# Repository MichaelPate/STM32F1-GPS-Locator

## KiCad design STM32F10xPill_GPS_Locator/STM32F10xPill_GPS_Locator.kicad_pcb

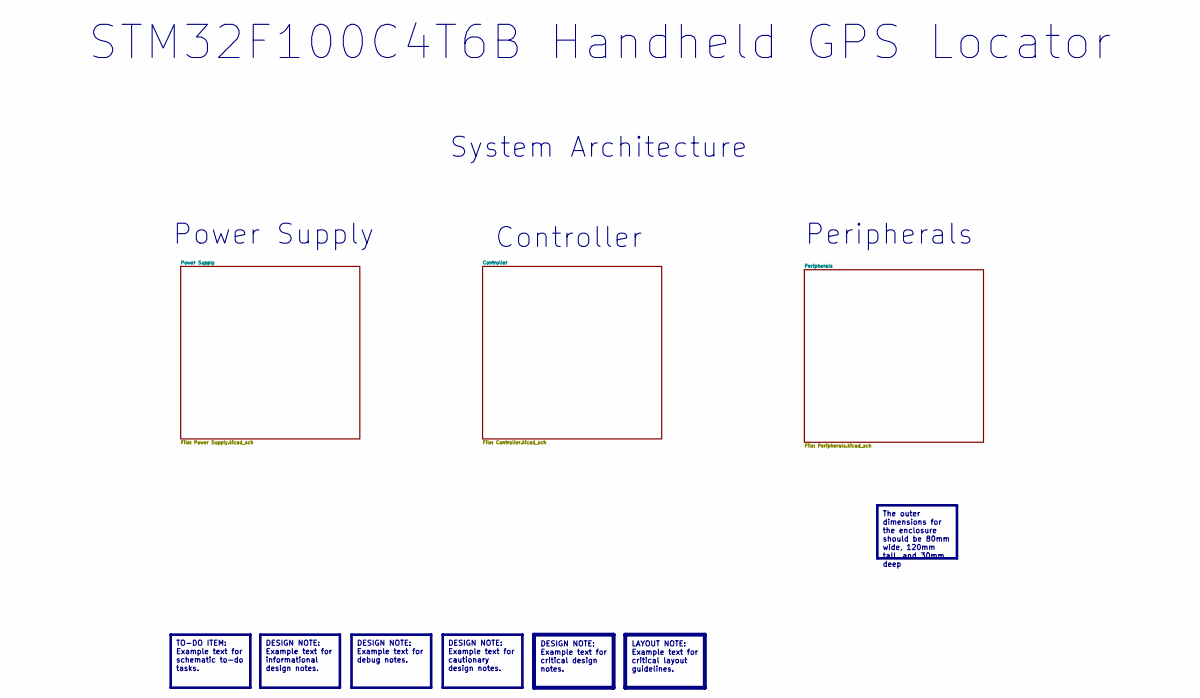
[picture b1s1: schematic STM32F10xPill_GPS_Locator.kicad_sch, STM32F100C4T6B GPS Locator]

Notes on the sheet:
STM32F100C4T6B Handheld GPS Locator
Peripherals
Controller
System Architecture
Power Supply
DESIGN NOTE: Example text for debug notes.
TO-DO ITEM: Example text for schematic to-do tasks.
The outer dimensions for the enclosure should be 80mm wide, 120mm tall, and 30mm deep
DESIGN NOTE: Example text for cautionary design notes.
DESIGN NOTE: Example text for critical design notes.
DESIGN NOTE: Example text for informational design notes.
LAYOUT NOTE: Example text for critical layout guidelines.

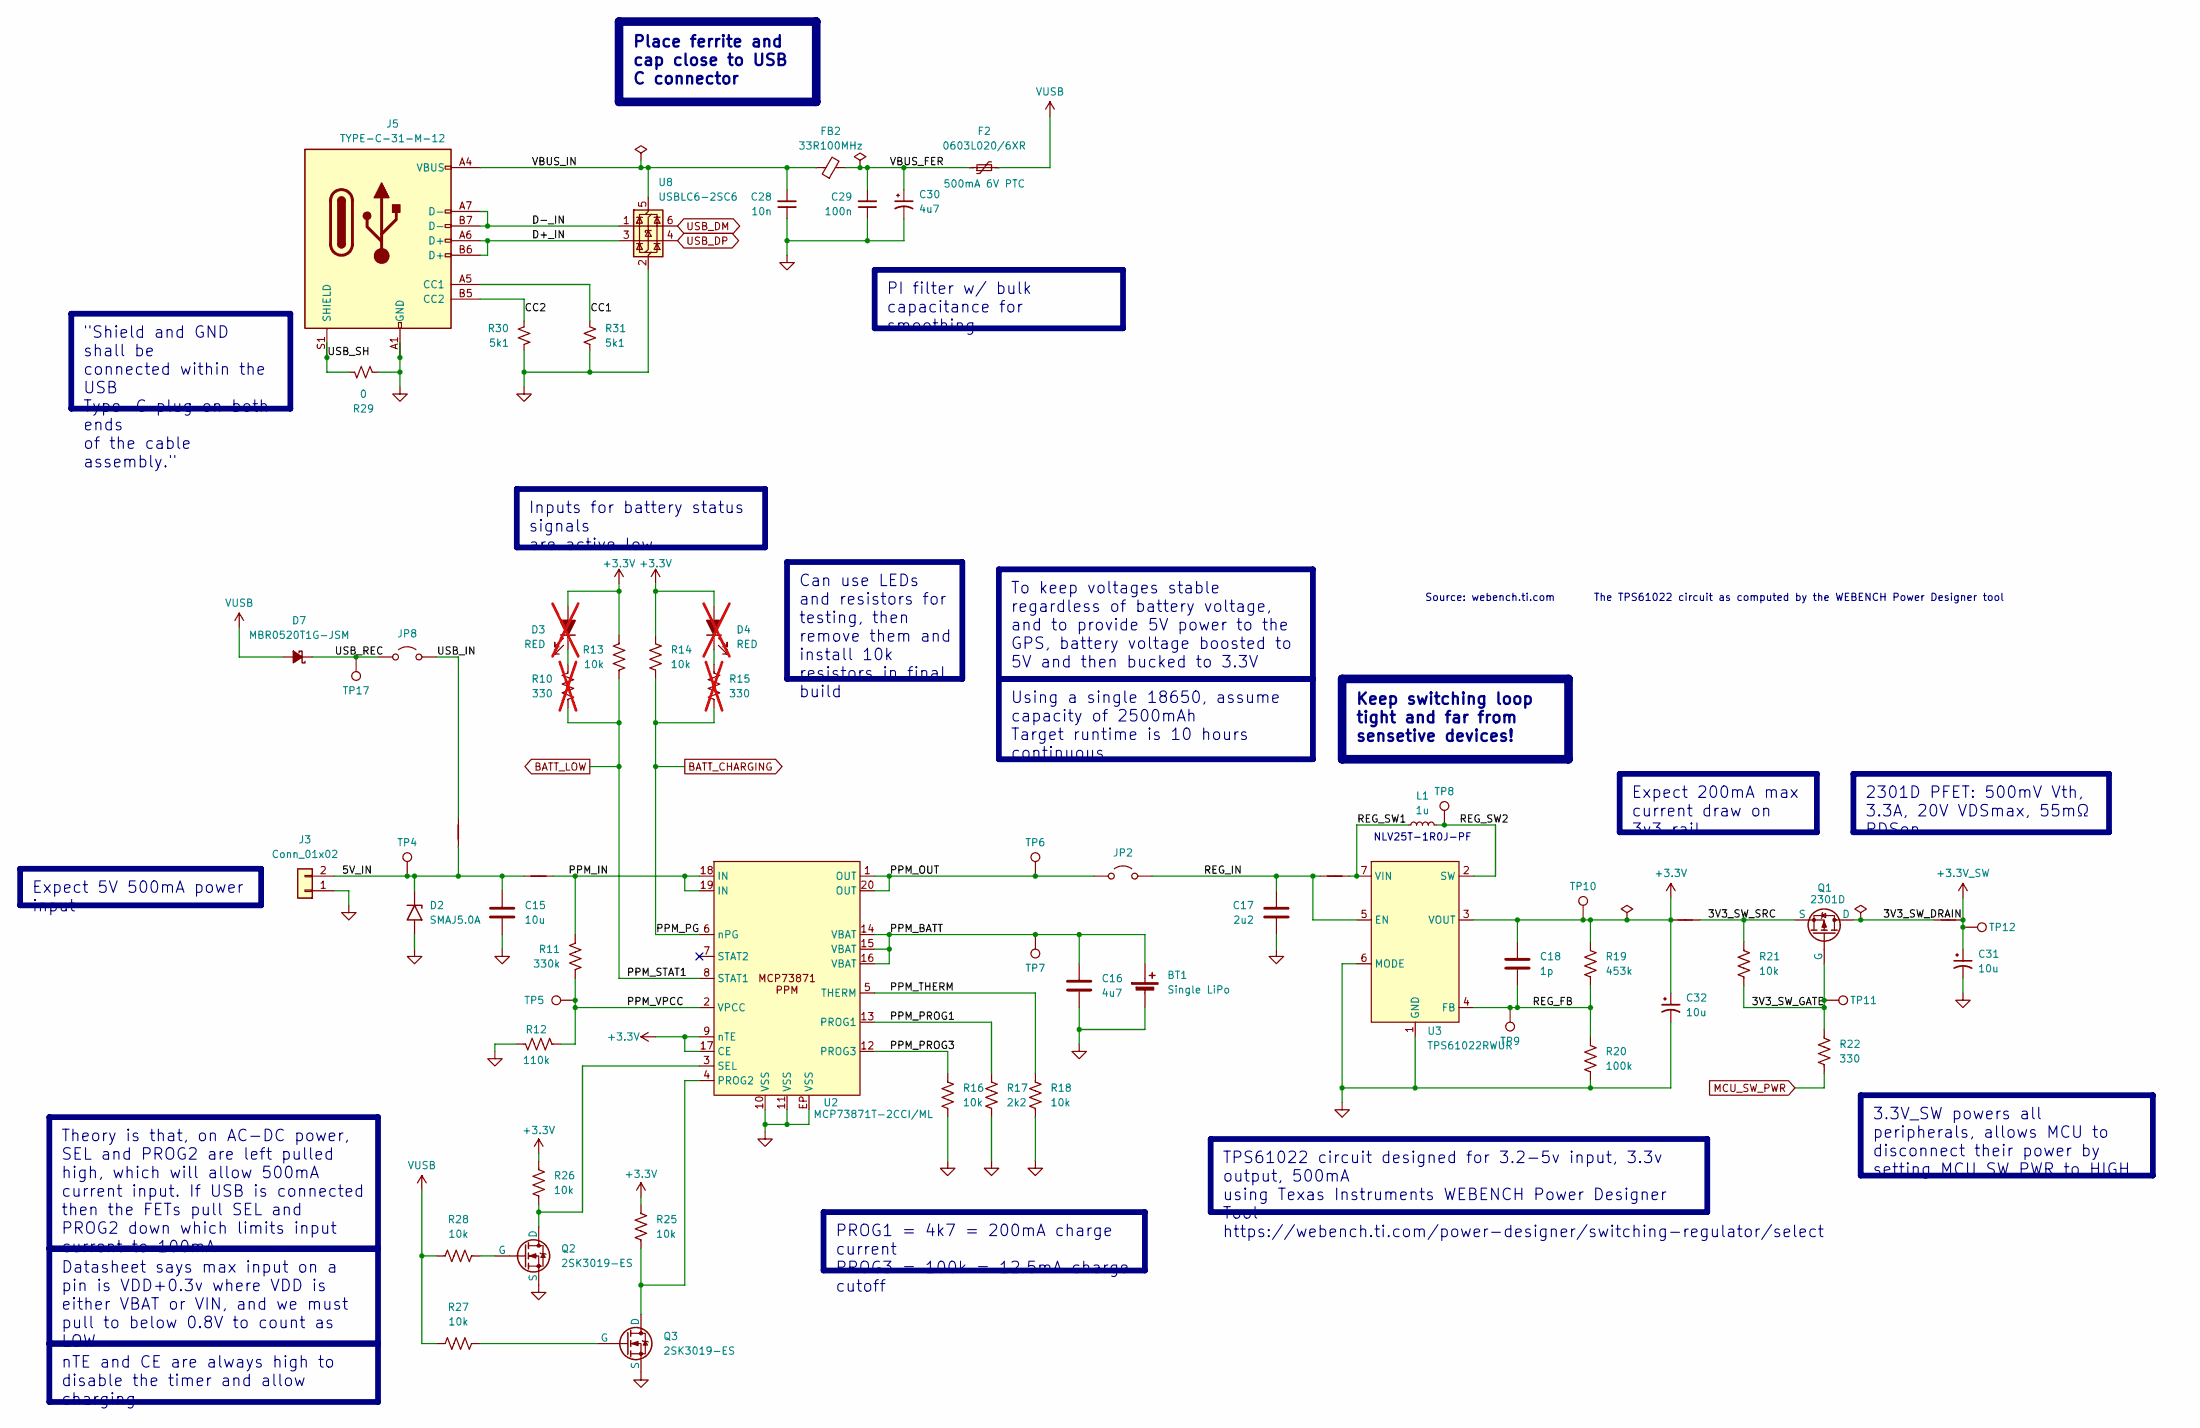
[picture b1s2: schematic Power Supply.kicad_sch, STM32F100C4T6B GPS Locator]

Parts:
BT1: Single LiPo; BatteryHolder_MPD_BH-18650-PC2
C15: 10u; C_0805_2012Metric
C16: 4u7; C_0805_2012Metric
C17: 2u2; C_0805_2012Metric
C18: 1p; C_0402_1005Metric
C28: 10n; C_0402_1005Metric
C29: 100n; C_0402_1005Metric
C30: 4u7; CP_Elec_4x5.4
C31, C32: 10u; CP_Elec_4x5.4
D2: SMAJ5.0A; D_SMA
D3, D4: RED; LED_0603_1608Metric; not fitted
D7: MBR0520T1G-JSM; D_SOD-123
F2: 0603L020/6XR; Fuse_0603_1608Metric_Pad1.05x0.95mm_HandSolder
FB2: 33R100MHz; L_0402_1005Metric
J3: Conn_01x02; JST_PH_B2B-PH-K_1x02_P2.00mm_Vertical
J5: TYPE-C-31-M-12; USB_C_Receptacle_HRO_TYPE-C-31-M-12; LCSC Part C165948
JP2, JP8: Jumper_2_Open; SolderJumper-2_P1.3mm_Open_Pad1.0x1.5mm
L1: 1u; L_1008_2520Metric; LCSC Part C76827
NT1, NT2, NT3, NT4, NT6: NetTie_2; NetTie-2_SMD_Pad0.5mm
Q1: 2301D; SOT-23; LCSC Part C7499855
Q2, Q3: 2SK3019-ES; SOT-523; LCSC Part 2SK3019-ES
R10, R15: 330; R_0402_1005Metric_Pad0.72x0.64mm_HandSolder; not fitted
R11: 330k; R_0402_1005Metric_Pad0.72x0.64mm_HandSolder
R12: 110k; R_0402_1005Metric_Pad0.72x0.64mm_HandSolder
R13, R14, R16, R18, R21, R25, R26, R27, R28: 10k; R_0402_1005Metric_Pad0.72x0.64mm_HandSolder
R17: 2k2; R_0402_1005Metric_Pad0.72x0.64mm_HandSolder
R19: 453k; R_0402_1005Metric_Pad0.72x0.64mm_HandSolder
R20: 100k; R_0402_1005Metric_Pad0.72x0.64mm_HandSolder
R22: 330; R_0402_1005Metric_Pad0.72x0.64mm_HandSolder
R29: 0; R_0402_1005Metric
R30, R31: 5k1; R_0402_1005Metric
TP4: 5V_IN; TestPoint_Pad_D1.5mm
TP5: PPM_VPCC; TestPoint_Pad_D1.5mm
TP6: PPM_OUT; TestPoint_Pad_D1.5mm
TP7: PPM_BATT; TestPoint_Pad_D1.5mm
TP8: REG_SW; TestPoint_Pad_D1.5mm
TP9: REG_FB; TestPoint_Pad_D1.5mm
TP10: REG_OUT; TestPoint_Pad_D1.5mm
TP11: 3V3_SW_GATE; TestPoint_Pad_D1.5mm
TP12: 3V3_SW; TestPoint_Pad_D1.5mm
TP17: USB_REC; TestPoint_Pad_D1.5mm
U2: MCP73871T-2CCI/ML; QFN-20-1EP_4x4mm_P0.5mm_EP2.5x2.5mm; LCSC Part C511310
U3: TPS61022RWUR; Texas_RWU0007A_VQFN-7_2x2mm_P0.5mm; LCSC Part C915088
U8: USBLC6-2SC6; SOT-23-6

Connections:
+3.3V: C18.2, C32.1, D3.2 (A), D4.2 (A), NT3.1, R13.2, R14.2, R19.2, R25.2, R26.2, TP10.1, U2.9 (nTE), U2.17 (CE), U3.3 (VOUT); also elsewhere on the board
+3.3V_SW: C31.1, NT4.2, TP12.1; also elsewhere on the board
/Power Supply/3V3_SW_DRAIN: NT4.1, Q1.1 (D)
/Power Supply/3V3_SW_GATE: Q1.2 (G), R21.1, R22.2, TP11.1
/Power Supply/3V3_SW_SRC: NT3.2, Q1.3 (S), R21.2
/Power Supply/5V_IN: C15.2, D2.1 (A1), J3.2, NT1.1, NT6.1, TP4.1
/Power Supply/CC1: J5.A5 (CC1), R31.2
/Power Supply/CC2: J5.B5 (CC2), R30.2
/Power Supply/D+_IN: J5.A6 (D+), J5.B6 (D+), U8.3 (I/O2)
/Power Supply/D-_IN: J5.A7 (D-), J5.B7 (D-), U8.1 (I/O1)
/Power Supply/PPM_BATT: BT1.1 (+), C16.2, TP7.1, U2.14 (VBAT), U2.15 (VBAT), U2.16 (VBAT)
/Power Supply/PPM_IN: NT1.2, R11.2, U2.18 (IN), U2.19 (IN)
/Power Supply/PPM_OUT: JP2.1 (A), TP6.1, U2.1 (OUT), U2.20 (OUT)
/Power Supply/PPM_PROG1: R17.2, U2.13 (PROG1)
/Power Supply/PPM_PROG3: R16.2, U2.12 (PROG3)
/Power Supply/PPM_THERM: R18.2, U2.5 (THERM)
/Power Supply/PPM_VPCC: R11.1, R12.1, TP5.1, U2.2 (VPCC)
/Power Supply/REG_FB: C18.1, R19.1, R20.2, TP9.1, U3.4 (FB)
/Power Supply/REG_IN: C17.2, JP2.2 (B), NT2.1, U3.5 (EN)
/Power Supply/REG_SW1: L1.2, NT2.2, U3.7 (VIN)
/Power Supply/REG_SW2: L1.1, TP8.1, U3.2 (SW)
/Power Supply/USB_IN: JP8.2 (B), NT6.2
/Power Supply/USB_REC: D7.1 (K), JP8.1 (A), TP17.1
/Power Supply/USB_SH: J5.S1 (SHIELD), R29.1
/Power Supply/VBUS_FER: C29.2, C30.1, F2.1, FB2.2
/Power Supply/VBUS_IN: C28.2, FB2.1, J5.A4 (VBUS), J5.A9 (VBUS), J5.B4 (VBUS), J5.B9 (VBUS), U8.5 (VBUS)
BATT_CHARGING: R14.1, R15.1, U2.6 (nPG); also elsewhere on the board
BATT_LOW: R10.1, R13.1, U2.8 (STAT1); also elsewhere on the board
GND: BT1.2 (-), C15.1, C16.1, C17.1, C28.1, C29.1, C30.2, C31.2, C32.2, D2.2 (A2), J3.1, J5.A1 (GND), J5.A12 (GND), J5.B1 (GND), J5.B12 (GND), Q2.3 (S), Q3.3 (S), R12.2, R16.1, R17.1, R18.1, R20.1, R29.2, R30.1, R31.1, U2.10 (VSS), U2.11 (VSS), U2.EP (VSS), U3.1 (GND), U3.6 (MODE), U8.2 (GND); also elsewhere on the board
MCU_SW_PWR: R22.1
unnamed: D3.1 (K), R10.2
unnamed: D4.1 (K), R15.2
unnamed: Q2.1 (D), R26.1, U2.3 (SEL)
unnamed: Q2.2 (G), R28.1
unnamed: Q3.1 (D), R25.1, U2.4 (PROG2)
unnamed: Q3.2 (G), R27.1
USB_DM: U8.6 (I/O1); also elsewhere on the board
USB_DP: U8.4 (I/O2); also elsewhere on the board
VUSB: D7.2 (A), F2.2, R27.2, R28.2

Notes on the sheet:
NLV25T-1R0J-PF
Source: webench.ti.com The TPS61022 circuit as computed by the WEBENCH Power Designer tool
2301D PFET: 500mV Vth, 3.3A, 20V VDSmax, 55mΩ RDSon
PROG1 = 4k7 = 200mA charge current PROG3 = 100k = 12.5mA charge cutoff
Inputs for battery status signals are active low
"Shield and GND shall be connected within the USB Type-C plug on both ends of the cable assembly."
Datasheet says max input on a pin is VDD+0.3v where VDD is either VBAT or VIN, and we must pull to below 0.8V to count as LOW
nTE and CE are always high to disable the timer and allow charging
Expect 200mA max current draw on 3v3 rail
Expect 5V 500mA power input
PI filter w/ bulk capacitance for smoothing
Using a single 18650, assume capacity of 2500mAh Target runtime is 10 hours continuous
To keep voltages stable regardless of battery voltage, and to provide 5V power to the GPS, battery voltage boosted to 5V and then bucked to 3.3V
Theory is that, on AC-DC power, SEL and PROG2 are left pulled high, which will allow 500mA current input. If USB is connected then the FETs pull SEL and PROG2 down which limits input current to 100mA
Can use LEDs and resistors for testing, then remove them and install 10k resistors in final build
3.3V_SW powers all peripherals, allows MCU to disconnect their power by setting MCU_SW_PWR to HIGH
Keep switching loop tight and far from sensetive devices!
Place ferrite and cap close to USB C connector
TPS61022 circuit designed for 3.2-5v input, 3.3v output, 500mA using Texas Instruments WEBENCH Power Designer Tool https://webench.ti.com/power-designer/switching-regulator/select

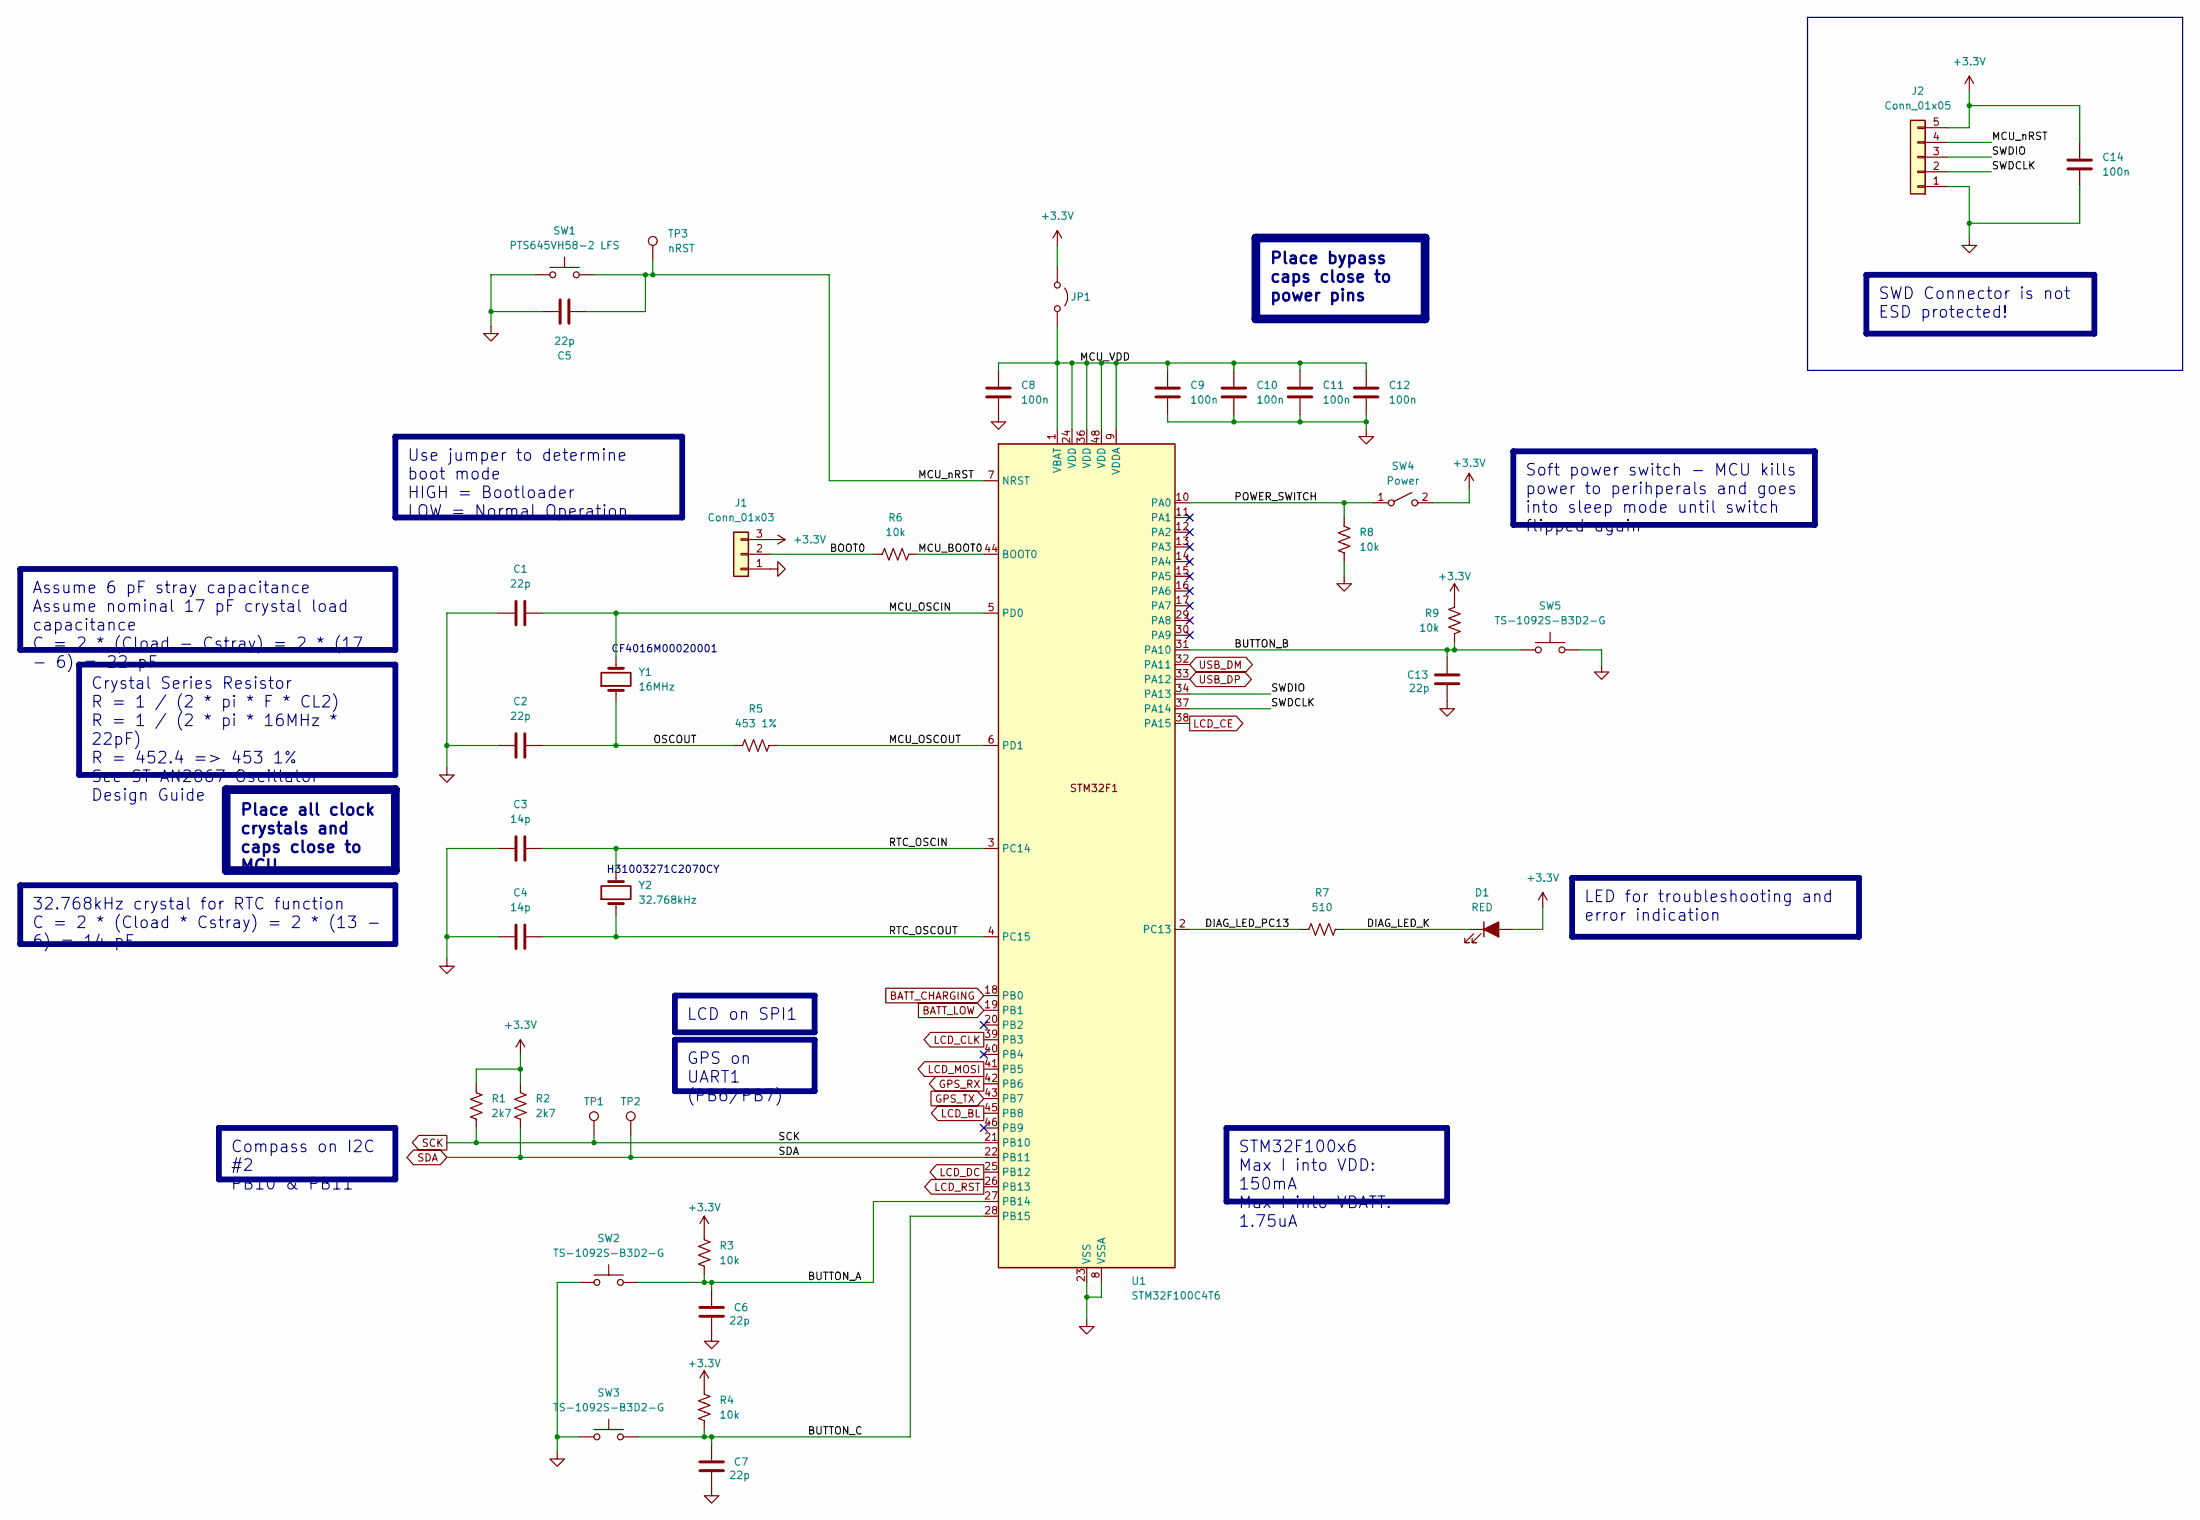
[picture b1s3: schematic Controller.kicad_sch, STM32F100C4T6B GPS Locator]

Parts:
C1, C2, C5, C6, C7, C13: 22p; C_0402_1005Metric
C3, C4: 14p; C_0402_1005Metric
C8: 100n; C_0603_1608Metric
C9, C10, C11, C12, C14: 100n; C_0402_1005Metric
D1: RED; LED_0603_1608Metric
J1: Conn_01x03; PinHeader_1x03_P2.54mm_Horizontal
J2: Conn_01x05; PinHeader_1x05_P2.54mm_Horizontal
JP1: Jumper_2_Open; SolderJumper-2_P1.3mm_Open_Pad1.0x1.5mm
R1, R2: 2k7; R_0402_1005Metric_Pad0.72x0.64mm_HandSolder
R3, R4, R6, R8, R9: 10k; R_0402_1005Metric_Pad0.72x0.64mm_HandSolder
R5: 453 1%; R_0402_1005Metric_Pad0.72x0.64mm_HandSolder
R7: 510; R_0402_1005Metric_Pad0.72x0.64mm_HandSolder
SW1: PTS645VH58-2 LFS; SW_Tactile_SPST_Angled_PTS645Vx58-2LFS; Digikey Part CKN9120-ND
SW2, SW3, SW5: TS-1092S-B3D2-G; SW_Tactile_SPST_NO_Straight_CK_PTS636Sx25SMTRLFS; LCSC Part C520860
SW4: Power; JST_PH_B2B-PH-K_1x02_P2.00mm_Vertical
TP1: SCK; TestPoint_Pad_D1.5mm
TP2: SDA; TestPoint_Pad_D1.5mm
TP3: nRST; TestPoint_Pad_D1.5mm
U1: STM32F100C4T6; LQFP-48_7x7mm_P0.5mm
Y1: 16MHz; Crystal_SMD_3225-4Pin_3.2x2.5mm; LCSC Part C7464895
Y2: 32.768kHz; Crystal_SMD_3215-2Pin_3.2x1.5mm; LCSC Part C5361379

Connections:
+3.3V: C14.2, D1.2 (A), J1.3, J2.5, JP1.1 (A), R1.2, R2.2, R3.2, R4.2, R9.2, SW4.2 (B); also elsewhere on the board
/Controller/BOOT0: J1.2, R6.1
/Controller/BUTTON_A: C6.2, R3.1, SW2.2, U1.27 (PB14)
/Controller/BUTTON_B: C13.2, R9.1, SW5.2, U1.31 (PA10)
/Controller/BUTTON_C: C7.2, R4.1, SW3.2, U1.28 (PB15)
/Controller/DIAG_LED_K: D1.1 (K), R7.1
/Controller/DIAG_LED_PC13: R7.2, U1.2 (PC13)
/Controller/MCU_BOOT0: R6.2, U1.44 (BOOT0)
/Controller/MCU_OSCIN: C1.2, U1.5 (PD0), Y1.3
/Controller/MCU_OSCOUT: R5.2, U1.6 (PD1)
/Controller/MCU_VDD: C8.2, C9.2, C10.2, C11.2, C12.2, JP1.2 (B), U1.1 (VBAT), U1.9 (VDDA), U1.24 (VDD), U1.36 (VDD), U1.48 (VDD)
/Controller/MCU_nRST: C5.2, J2.4, SW1.2, TP3.1, U1.7 (NRST)
/Controller/OSCOUT: C2.2, R5.1, Y1.1
/Controller/POWER_SWITCH: R8.2, SW4.1 (A), U1.10 (PA0)
/Controller/RTC_OSCIN: C3.2, U1.3 (PC14), Y2.2
/Controller/RTC_OSCOUT: C4.2, U1.4 (PC15), Y2.1
/Controller/SWDCLK: J2.2, U1.37 (PA14)
/Controller/SWDIO: J2.3, U1.34 (PA13)
BATT_CHARGING: U1.18 (PB0); also elsewhere on the board
BATT_LOW: U1.19 (PB1); also elsewhere on the board
GND: C1.1, C2.1, C3.1, C4.1, C5.1, C6.1, C7.1, C8.1, C9.1, C10.1, C11.1, C12.1, C13.1, C14.1, J1.1, J2.1, R8.1, SW1.1, SW2.1, SW3.1, SW5.1, U1.8 (VSSA), U1.23 (VSS), U1.35 (VSS), U1.47 (VSS); also elsewhere on the board
GPS_RX: U1.42 (PB6)
GPS_TX: U1.43 (PB7); also elsewhere on the board
LCD_BL: U1.45 (PB8); also elsewhere on the board
LCD_CE: U1.38 (PA15); also elsewhere on the board
LCD_CLK: U1.39 (PB3); also elsewhere on the board
LCD_DC: U1.25 (PB12); also elsewhere on the board
LCD_MOSI: U1.41 (PB5); also elsewhere on the board
LCD_RST: U1.26 (PB13); also elsewhere on the board
SCK: R1.1, TP1.1, U1.21 (PB10); also elsewhere on the board
SDA: R2.1, TP2.1, U1.22 (PB11); also elsewhere on the board
USB_DM: U1.32 (PA11); also elsewhere on the board
USB_DP: U1.33 (PA12); also elsewhere on the board

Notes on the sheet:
H31003271C2070CY
CF4016M00020001
Crystal Series Resistor R = 1 / (2 * pi * F * CL2) R = 1 / (2 * pi * 16MHz * 22pF) R = 452.4 => 453 1% See ST AN2867 Oscillator Design Guide
Place all clock crystals and caps close to MCU
STM32F100x6 Max I into VDD: 150mA Max I into VBATT: 1.75uA
Soft power switch - MCU kills power to perihperals and goes into sleep mode until switch flipped again
LCD on SPI1
Compass on I2C #2 PB10 & PB11
GPS on UART1 (PB6/PB7)
Place bypass caps close to power pins
Use jumper to determine boot mode HIGH = Bootloader LOW = Normal Operation
LED for troubleshooting and error indication
Assume 6 pF stray capacitance Assume nominal 17 pF crystal load capacitance C = 2 * (Cload - Cstray) = 2 * (17 - 6) = 22 pF
SWD Connector is not ESD protected!
32.768kHz crystal for RTC function C = 2 * (Cload * Cstray) = 2 * (13 - 6) = 14 pF

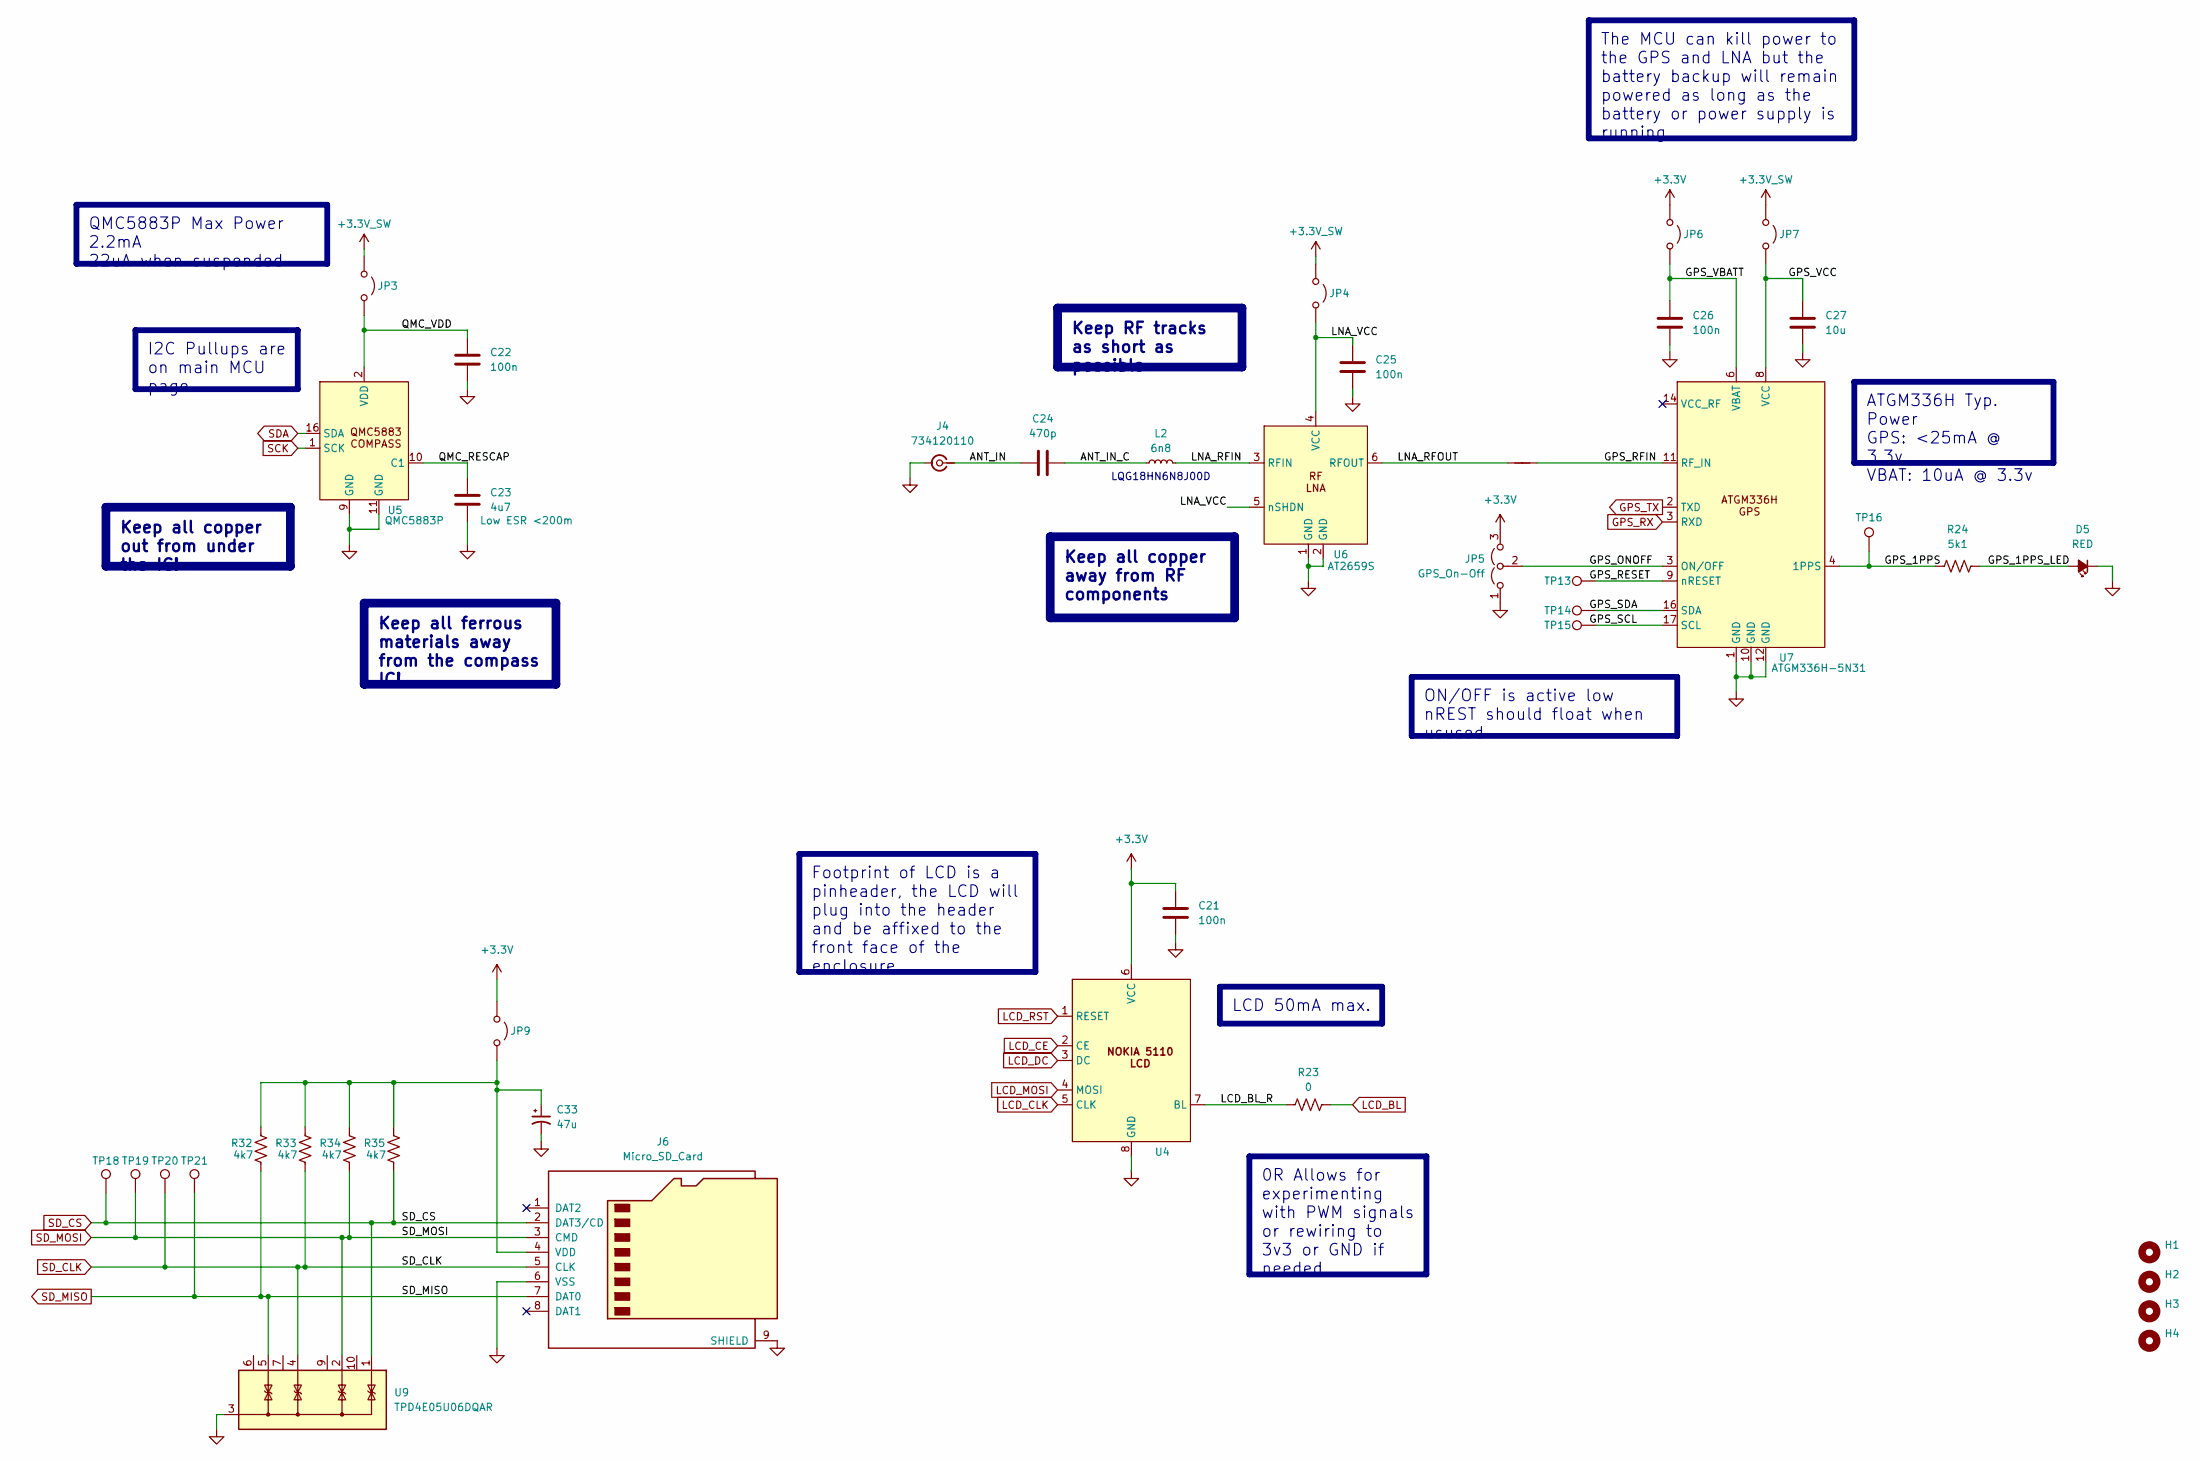
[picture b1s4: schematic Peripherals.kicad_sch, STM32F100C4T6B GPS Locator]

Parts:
C21, C22, C25, C26: 100n; C_0603_1608Metric
C23: 4u7; C_0805_2012Metric
C24: 470p; C_0402_1005Metric
C27: 10u; C_0805_2012Metric
C33: 47u; CP_Elec_4x5.4
D5: RED; LED_0603_1608Metric
H1, H2, H3, H4: MountingHole; MountingHole_2.2mm_M2
J4: 734120110; U.FL_Molex_MCRF_73412-0110_Vertical; LCSC Part C434806
J6: Micro_SD_Card; microSD_HC_Hirose_DM3AT-SF-PEJM5
JP3, JP4, JP6, JP7, JP9: Jumper_2_Open; SolderJumper-2_P1.3mm_Open_Pad1.0x1.5mm
JP5: GPS_On-Off; SolderJumper-3_P1.3mm_Open_Pad1.0x1.5mm_NumberLabels
L2: 6n8; L_0603_1608Metric; LCSC Part C882493
NT5: NetTie_2; NetTie-2_SMD_Pad0.5mm
R23: 0; R_0402_1005Metric_Pad0.72x0.64mm_HandSolder
R24: 5k1; R_0402_1005Metric_Pad0.72x0.64mm_HandSolder
R32, R33, R34, R35: 4k7; R_0402_1005Metric_Pad0.72x0.64mm_HandSolder
TP13: GPS_nRESET; TestPoint_Pad_D1.5mm
TP14: GPS_SDA; TestPoint_Pad_D1.5mm
TP15: GPS_SCL; TestPoint_Pad_D1.5mm
TP16: GPS_1PPS; TestPoint_Pad_D1.5mm
TP18: SD_CS; TestPoint_Pad_D1.5mm
TP19: SD_MOSI; TestPoint_Pad_D1.5mm
TP20: SD_CLK; TestPoint_Pad_D1.5mm
TP21: SD_MISO; TestPoint_Pad_D1.5mm
U4: PinSocket_1x08_P2.54mm_Vertical
U5: QMC5883P; LGA-16_3x3mm_P0.5mm; LCSC Part C2847467
U6: AT2659S; SOT-23-6; LCSC Part C883443
U7: ATGM336H-5N31; ATGM336H_SMD_9.7x10.1mm; LCSC Part C90770
U9: TPD4E05U06DQAR; Diodes_UDFN-10_1.0x2.5mm_P0.5mm; LCSC Part C22390021

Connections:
+3.3V: C21.2, JP5.3 (B), JP6.1 (A), JP9.1 (A), U4.6 (VCC); also elsewhere on the board
+3.3V_SW: JP3.1 (A), JP4.1 (A), JP7.1 (A); also elsewhere on the board
/Peripherals/ANT_IN: C24.2, J4.1 (In)
/Peripherals/ANT_IN_C: C24.1, L2.2
/Peripherals/GPS_1PPS: R24.1, TP16.1, U7.4 (1PPS)
/Peripherals/GPS_1PPS_LED: D5.2 (A), R24.2
/Peripherals/GPS_RFIN: NT5.2, U7.11 (RF_IN)
/Peripherals/GPS_VBATT: C26.2, JP6.2 (B), U7.6 (VBAT)
/Peripherals/GPS_VCC: C27.2, JP7.2 (B), U7.8 (VCC)
/Peripherals/LCD_BL_R: R23.1, U4.7 (BL)
/Peripherals/LNA_RFIN: L2.1, U6.3 (RFIN)
/Peripherals/LNA_RFOUT: NT5.1, U6.6 (RFOUT)
/Peripherals/LNA_VCC: C25.2, JP4.2 (B), U6.4 (VCC), U6.5 (nSHDN)
/Peripherals/QMC_RESCAP: C23.2, U5.10 (C1)
/Peripherals/QMC_VDD: C22.2, JP3.2 (B), U5.2 (VDD)
GND: C21.1, C22.1, C23.1, C25.1, C26.1, C27.1, C33.2, D5.1 (K), J4.2 (Ext), J6.6 (VSS), J6.9 (SHIELD), JP5.1 (A), U4.8 (GND), U5.9 (GND), U5.11 (GND), U6.1 (GND), U6.2 (GND), U7.1 (GND), U7.10 (GND), U7.12 (GND), U9.3 (G), U9.8 (G); also elsewhere on the board
GPS_TX: U7.2 (TXD); also elsewhere on the board
LCD_BL: R23.2; also elsewhere on the board
LCD_CE: U4.2 (CE); also elsewhere on the board
LCD_CLK: U4.5 (CLK); also elsewhere on the board
LCD_DC: U4.3 (DC); also elsewhere on the board
LCD_MOSI: U4.4 (MOSI); also elsewhere on the board
LCD_RST: U4.1 (RESET); also elsewhere on the board
unnamed: C33.1, J6.4 (VDD), JP9.2 (B), R32.2, R33.2, R34.2, R35.2
unnamed: TP15.1, U7.17 (SCL)
unnamed: TP14.1, U7.16 (SDA)
unnamed: TP13.1, U7.9 (nRESET)
SCK: U5.1 (SCK); also elsewhere on the board
SDA: U5.16 (SDA); also elsewhere on the board
SD_CLK: J6.5 (CLK), R33.1, TP20.1, U9.4 (IO3)
SD_CS: J6.2 (DAT3/CD), R35.1, TP18.1, U9.1 (IO1)
SD_MISO: J6.7 (DAT0), R32.1, TP21.1, U9.5 (IO4)
SD_MOSI: J6.3 (CMD), R34.1, TP19.1, U9.2 (IO2)

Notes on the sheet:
LQG18HN6N8J00D
ATGM336H Typ. Power GPS: <25mA @ 3.3v VBAT: 10uA @ 3.3v
Keep all ferrous materials away from the compass IC!
I2C Pullups are on main MCU page
The MCU can kill power to the GPS and LNA but the battery backup will remain powered as long as the battery or power supply is running
Keep RF tracks as short as possible
QMC5883P Max Power 2.2mA 22uA when suspended
0R Allows for experimenting with PWM signals or rewiring to 3v3 or GND if needed
LCD 50mA max.
Footprint of LCD is a pinheader, the LCD will plug into the header and be affixed to the front face of the enclosure
Keep all copper away from RF components
Keep all copper out from under the IC!
ON/OFF is active low nREST should float when usused

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
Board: 4 copper layers, 144 parts (6 on the bottom side), 86 nets, no tracks yet.

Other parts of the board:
C19, C20: 2u2; C_0603_1608Metric

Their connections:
+3.3V: C19.2; also elsewhere on the board
+3.3V_SW: C20.2; also elsewhere on the board
GND: C19.1, C20.1; also elsewhere on the board

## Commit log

2025-03-07 Initial Commit Empty Project
2025-03-07 Project Structure
2025-03-07 Add controller and clocks
2025-03-07 Tuned oscillator components
    Made more accurate according to the device datasheet as well as AN2867
2025-03-07 Updated text notes for main system oscillator
2025-03-07 Add schematic reset, boot, SWD, and some peripherals
2025-03-10 Add notes and clean up schematic
2025-03-20 add gitignore
2025-03-21 Add library parts for peripherals
2025-03-21 Switch from NEO-6m GPS to ATGM336H-5N31
    The neo-6m is EOL and not readily available as an IC module
2025-03-21 Work on adding GPS and Compass Peripherals
2025-03-21 ignore kiCad lock files
2025-03-22 Schematic is largely complete
2025-03-22 Updated net names, submit schematic for feedback
    After feedback is incorporated, PCB layout is ready to begin
2025-03-22 Cleaned up and submitted for review
2025-03-23 Add all footprints and symbols, retouch schametic
2025-03-23 Begin PCB layout
2025-03-23 Initial placement completed
2025-03-23 change text
2025-03-23 Add USB Port
    Added schematic for controlling SEL and PROG2 on the PPM, as well as USB filtering and ESD protection and stuff. The board layout was not changed yet
2025-03-23 Added SD card and updated PCB layout
2025-03-23 Small changes to pcb
2025-03-23 Add watermark footprint library to project
